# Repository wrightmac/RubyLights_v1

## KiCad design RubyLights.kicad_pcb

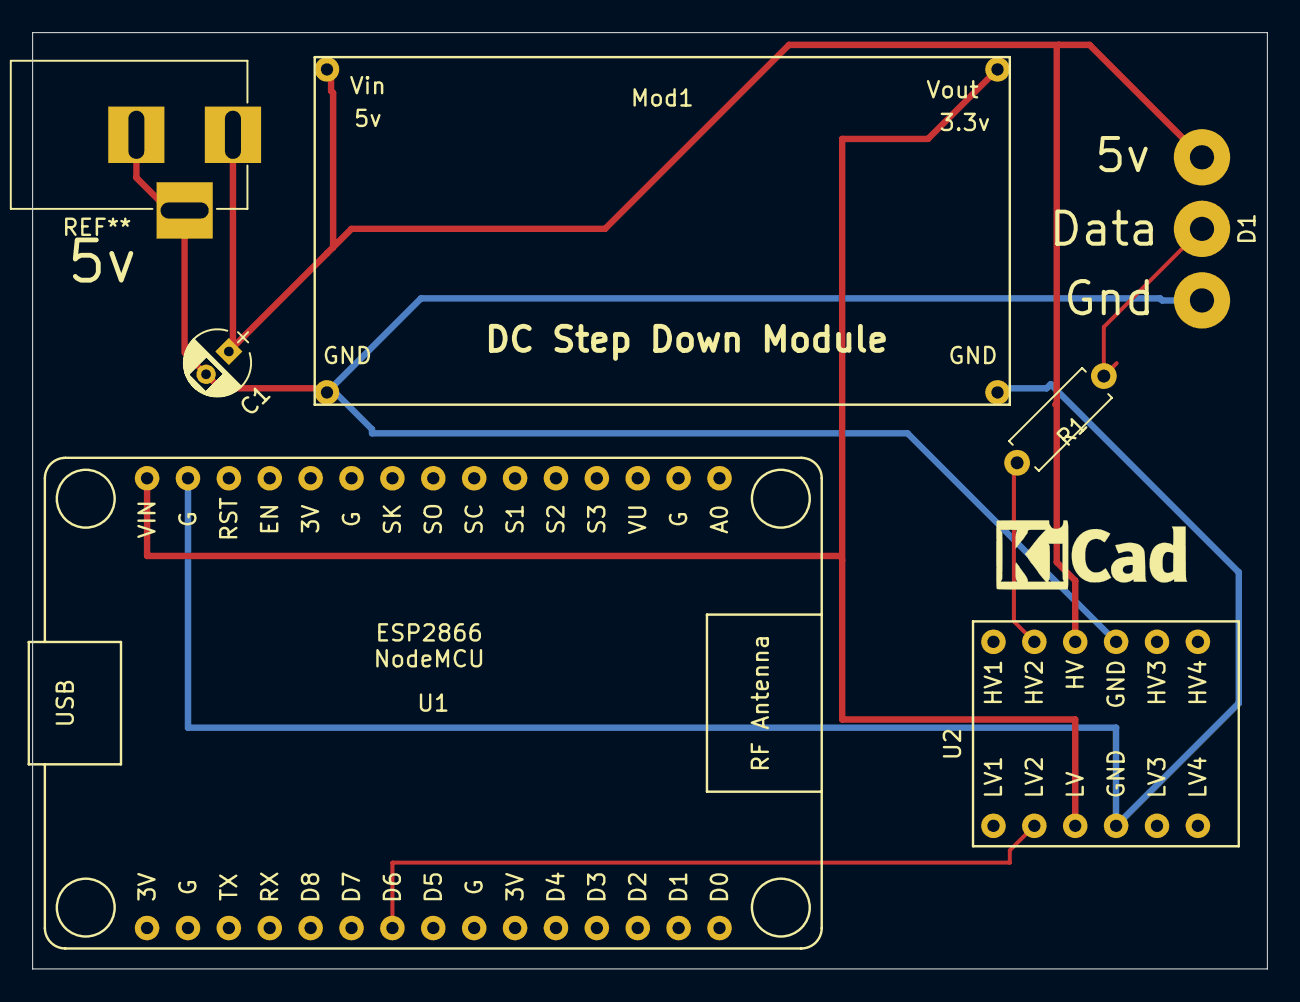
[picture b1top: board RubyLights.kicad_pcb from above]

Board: 2 copper layers, 76.7 x 58.2 mm, 6 parts (0 on the bottom side), 4 nets.

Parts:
C1: 1000uF; CP_Radial_D4.0mm_P2.00mm
D1: NeoPixel_THT; SolderWirePad_3x_1-5mmDrill
Mod1: LM2596_Mod; LM25965Module
R1: 300; R_Axial_DIN0207_L6.3mm_D2.5mm_P7.62mm_Horizontal
U1: NodeMCU1.0(ESP-12E); NodeMCU1.0(12-E)
U2: TXB0104RUT; LevelShifter4Chan

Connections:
+5V: C1.1, D1.1, U2.10
/3.3v: U1.15, U2.3
/Data: D1.2, R1.2, U1.22, U2.2, U2.11
GND: C1.2, D1.3, Mod1.2, U1.14, U2.4, U2.9

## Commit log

2019-06-05 LearningGitHub
